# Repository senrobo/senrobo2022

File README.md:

# Sentinels Robotics

Yay we passed the 100th commit milestone
400 Commit milestone

## Checklist

### Mechanical

- Kicker Done on 20/1/2022

### Parts used

| Part Name    | Part Description                                               |
| ------------ | -------------------------------------------------------------- |
| OpenMV H7/R7 | Camera                                                         |
| MUX          | Multiplexer (https://www.ti.com/lit/ds/symlink/cd74hc4067.pdf) |

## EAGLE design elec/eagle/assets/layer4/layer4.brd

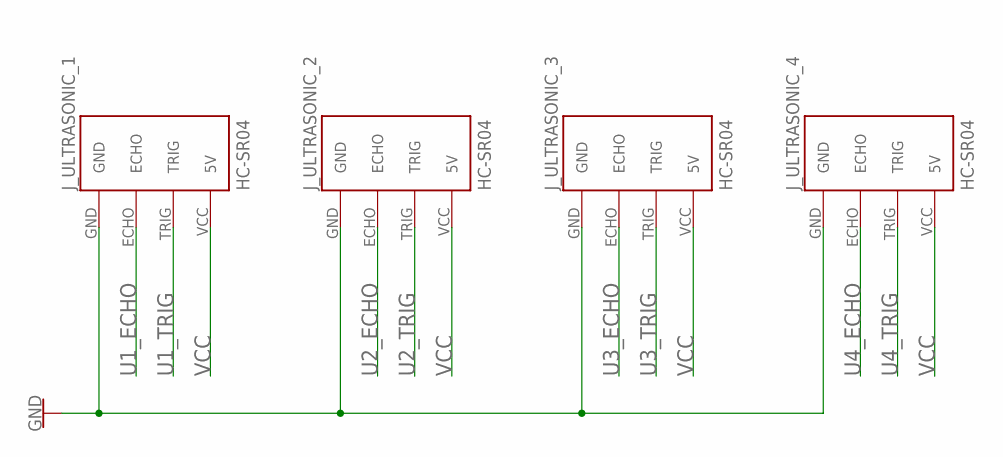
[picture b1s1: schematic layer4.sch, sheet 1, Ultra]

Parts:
J_ULTRASONIC_1, J_ULTRASONIC_2, J_ULTRASONIC_3, J_ULTRASONIC_4: HC-SR04; HC-SR04_FOOTPRINT

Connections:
GND: J_ULTRASONIC_1.GND, J_ULTRASONIC_2.GND, J_ULTRASONIC_3.GND, J_ULTRASONIC_4.GND; also elsewhere on the board
U1_ECHO: J_ULTRASONIC_1.ECHO; also elsewhere on the board
U1_TRIG: J_ULTRASONIC_1.TRIG; also elsewhere on the board
U2_ECHO: J_ULTRASONIC_2.ECHO; also elsewhere on the board
U2_TRIG: J_ULTRASONIC_2.TRIG; also elsewhere on the board
U3_ECHO: J_ULTRASONIC_3.ECHO; also elsewhere on the board
U3_TRIG: J_ULTRASONIC_3.TRIG; also elsewhere on the board
U4_ECHO: J_ULTRASONIC_4.ECHO; also elsewhere on the board
U4_TRIG: J_ULTRASONIC_4.TRIG; also elsewhere on the board
VCC: J_ULTRASONIC_1.VCC (5V), J_ULTRASONIC_2.VCC (5V), J_ULTRASONIC_3.VCC (5V), J_ULTRASONIC_4.VCC (5V); also elsewhere on the board

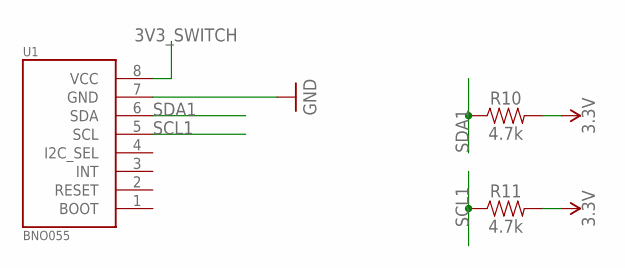
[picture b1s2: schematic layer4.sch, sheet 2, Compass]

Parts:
R10, R11: 4.7k; 0603
U1: BNO055

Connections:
3.3V: R10.2, R11.2
3V3_SWITCH: U1.8 (VCC); also elsewhere on the board
GND: U1.7 (GND); also elsewhere on the board
SCL1: R11.1, U1.5 (SCL); also elsewhere on the board
SDA1: R10.1, U1.6 (SDA); also elsewhere on the board

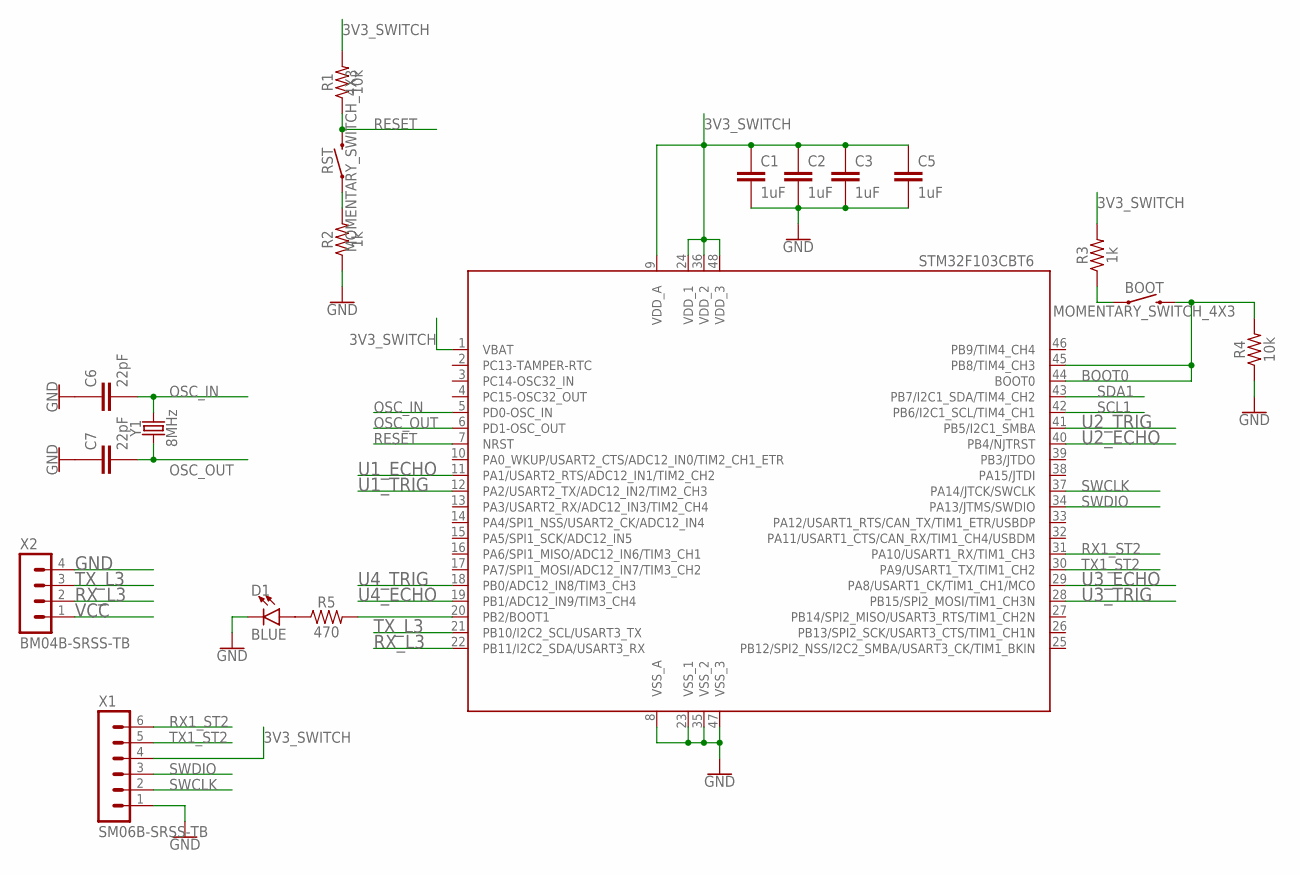
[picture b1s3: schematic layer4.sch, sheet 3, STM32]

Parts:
BOOT: MOMENTARY_SWITCH_4X3
C1, C2, C3, C5: 1uF; C0603
C6, C7: 22pF; C0603
D1: BLUE; LED-0603
R1, R4: 10k; R0603
R2, R3: 1k; R0603
R5: 470; R0603
RST: MOMENTARY_SWITCH_4X3
STM32_IR: STM32F103CBT6; LQFP48
X1: SM06B-SRSS-TB
X2: BM04B-SRSS-TB
Y1: 8MHz; CRYSTAL-SMD-5X3.2-2PAD

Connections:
3V3_SWITCH: C1.1, C2.1, C3.1, C5.2, R1.2, R3.2, STM32_IR.1 (VBAT), STM32_IR.9 (VDD_A), STM32_IR.24 (VDD_1), STM32_IR.36 (VDD_2), STM32_IR.48 (VDD_3), X1.4; also elsewhere on the board
BOOT0: BOOT.P$2 (2), R4.2, STM32_IR.44 (BOOT0), STM32_IR.45 (PB8/TIM4_CH3)
GND: C1.2, C2.2, C3.2, C5.1, C6.1, C7.1, D1.C, R2.1, R4.1, STM32_IR.8 (VSS_A), STM32_IR.23 (VSS_1), STM32_IR.35 (VSS_2), STM32_IR.47 (VSS_3), X1.1, X2.4; also elsewhere on the board
unnamed: R2.2, RST.P$1 (1)
unnamed: BOOT.P$1 (1), R3.1
unnamed: R5.2, STM32_IR.20 (PB2/BOOT1)
unnamed: D1.A, R5.1
OSC_IN: C6.2, STM32_IR.5 (PD0-OSC_IN), Y1.P$2 (2)
OSC_OUT: C7.2, STM32_IR.6 (PD1-OSC_OUT), Y1.P$1 (1)
RESET: R1.1, RST.P$2 (2), STM32_IR.7 (NRST)
RX1_ST2: STM32_IR.31 (PA10/USART1_RX/TIM1_CH3), X1.6
RX_L3: STM32_IR.22 (PB11/I2C2_SDA/USART3_RX), X2.2
SCL1: STM32_IR.42 (PB6/I2C1_SCL/TIM4_CH1); also elsewhere on the board
SDA1: STM32_IR.43 (PB7/I2C1_SDA/TIM4_CH2); also elsewhere on the board
SWCLK: STM32_IR.37 (PA14/JTCK/SWCLK), X1.2
SWDIO: STM32_IR.34 (PA13/JTMS/SWDIO), X1.3
TX1_ST2: STM32_IR.30 (PA9/USART1_TX/TIM1_CH2), X1.5
TX_L3: STM32_IR.21 (PB10/I2C2_SCL/USART3_TX), X2.3
U1_ECHO: STM32_IR.11 (PA1/USART2_RTS/ADC12_IN1/TIM2_CH2); also elsewhere on the board
U1_TRIG: STM32_IR.12 (PA2/USART2_TX/ADC12_IN2/TIM2_CH3); also elsewhere on the board
U2_ECHO: STM32_IR.40 (PB4/NJTRST); also elsewhere on the board
U2_TRIG: STM32_IR.41 (PB5/I2C1_SMBA); also elsewhere on the board
U3_ECHO: STM32_IR.29 (PA8/USART1_CK/TIM1_CH1/MCO); also elsewhere on the board
U3_TRIG: STM32_IR.28 (PB15/SPI2_MOSI/TIM1_CH3N); also elsewhere on the board
U4_ECHO: STM32_IR.19 (PB1/ADC12_IN9/TIM3_CH4); also elsewhere on the board
U4_TRIG: STM32_IR.18 (PB0/ADC12_IN8/TIM3_CH3); also elsewhere on the board
VCC: X2.1; also elsewhere on the board

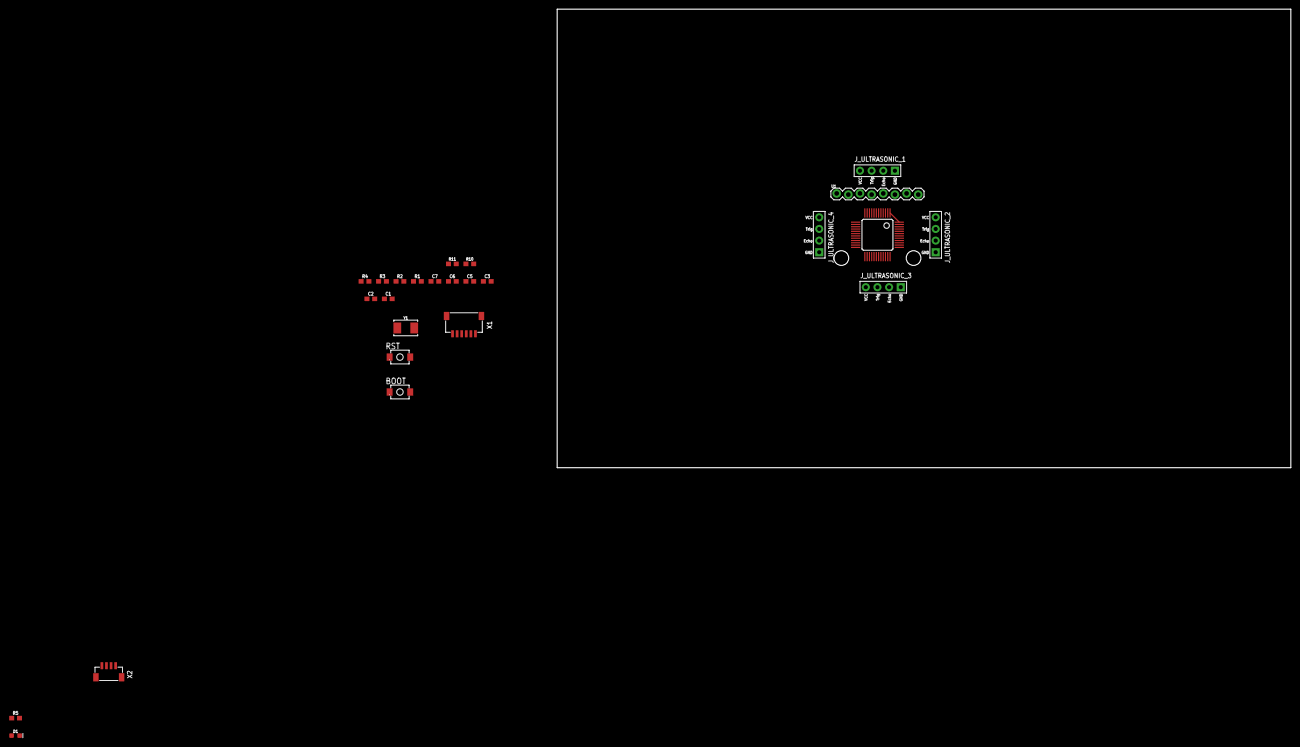
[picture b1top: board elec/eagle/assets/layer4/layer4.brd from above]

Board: 2 copper layers, 160.0 x 100.0 mm, 25 parts (0 on the bottom side), 28 nets.

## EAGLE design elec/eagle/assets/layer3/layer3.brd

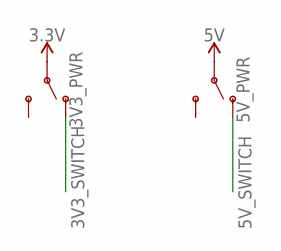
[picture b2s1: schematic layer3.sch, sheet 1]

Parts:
3V3_PWR, 5V_PWR: SWITCH-SPDT-PTH-11.6X4.0MM-LOCK; SWITCH_SPDT_PTH_11.6X4.0MM_LOCK

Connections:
3.3V: 3V3_PWR.2; also elsewhere on the board
3V3_SWITCH: 3V3_PWR.1 (O); also elsewhere on the board
5V: 5V_PWR.2; also elsewhere on the board
5V_SWITCH: 5V_PWR.1 (O); also elsewhere on the board

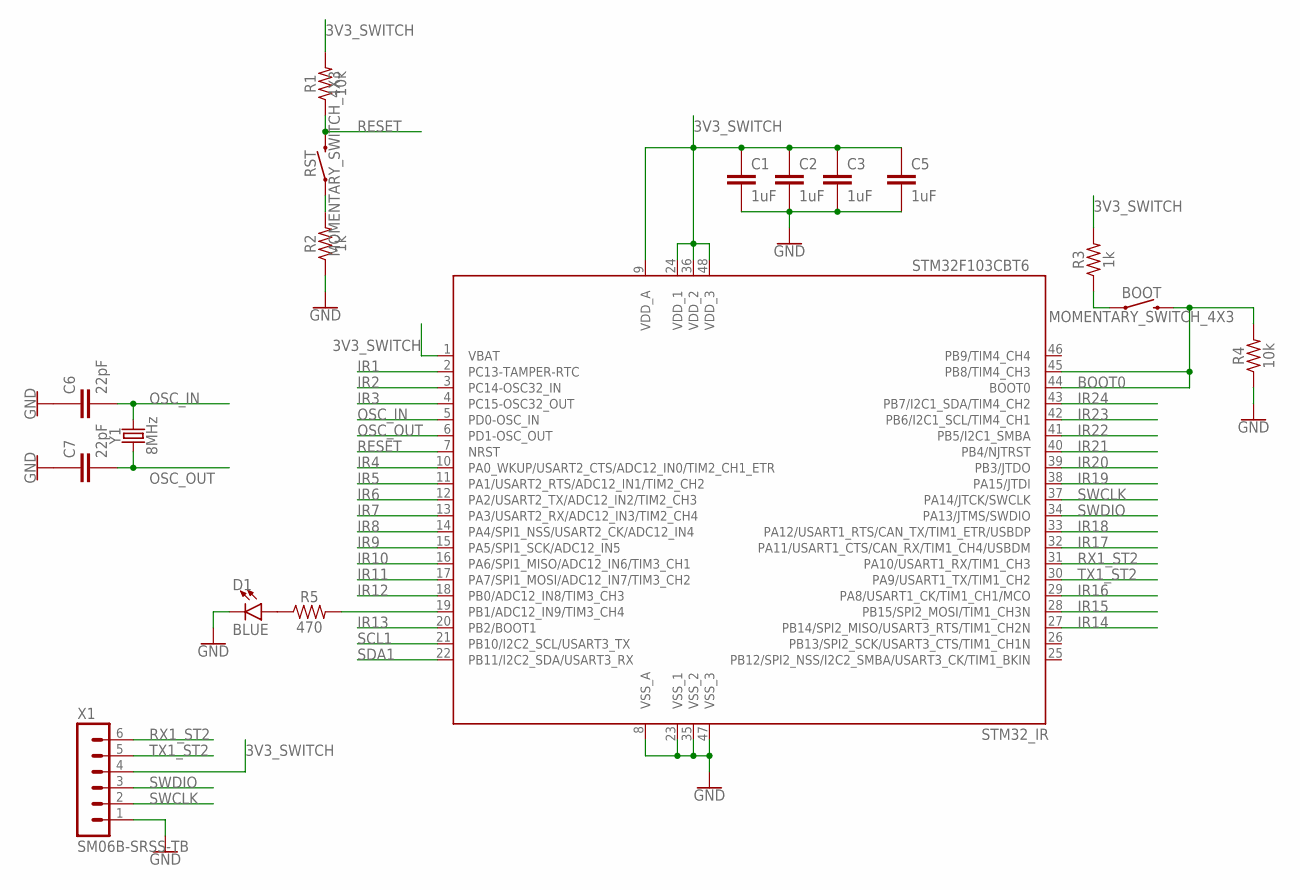
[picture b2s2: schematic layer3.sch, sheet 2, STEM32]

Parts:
BOOT: MOMENTARY_SWITCH_4X3
C1, C2, C3, C5: 1uF; C0603
C6, C7: 22pF; C0603
D1: BLUE; LED-0603
R1, R4: 10k; R0603
R2, R3: 1k; R0603
R5: 470; R0603
RST: MOMENTARY_SWITCH_4X3
STM32_IR: STM32F103CBT6; LQFP48
X1: SM06B-SRSS-TB
Y1: 8MHz; CRYSTAL-SMD-5X3.2-2PAD

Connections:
3V3_SWITCH: C1.1, C2.1, C3.1, C5.2, R1.2, R3.2, STM32_IR.1 (VBAT), STM32_IR.9 (VDD_A), STM32_IR.24 (VDD_1), STM32_IR.36 (VDD_2), STM32_IR.48 (VDD_3), X1.4; also elsewhere on the board
BOOT0: BOOT.P$2 (2), R4.2, STM32_IR.44 (BOOT0), STM32_IR.45 (PB8/TIM4_CH3)
GND: C1.2, C2.2, C3.2, C5.1, C6.1, C7.1, D1.C, R2.1, R4.1, STM32_IR.8 (VSS_A), STM32_IR.23 (VSS_1), STM32_IR.35 (VSS_2), STM32_IR.47 (VSS_3), X1.1; also elsewhere on the board
IR1: STM32_IR.2 (PC13-TAMPER-RTC); also elsewhere on the board
IR2: STM32_IR.3 (PC14-OSC32_IN); also elsewhere on the board
IR3: STM32_IR.4 (PC15-OSC32_OUT); also elsewhere on the board
IR4: STM32_IR.10 (PA0_WKUP/USART2_CTS/ADC12_IN0/TIM2_CH1_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); also elsewhere on the board
IR5: STM32_IR.11 (PA1/USART2_RTS/ADC12_IN1/TIM2_CH2); also elsewhere on the board
IR6: STM32_IR.12 (PA2/USART2_TX/ADC12_IN2/TIM2_CH3); also elsewhere on the board
IR7: STM32_IR.13 (PA3/USART2_RX/ADC12_IN3/TIM2_CH4); also elsewhere on the board
IR8: STM32_IR.14 (PA4/SPI1_NSS/USART2_CK/ADC12_IN4); also elsewhere on the board
IR9: STM32_IR.15 (PA5/SPI1_SCK/ADC12_IN5); also elsewhere on the board
IR10: STM32_IR.16 (PA6/SPI1_MISO/ADC12_IN6/TIM3_CH1); also elsewhere on the board
IR11: STM32_IR.17 (PA7/SPI1_MOSI/ADC12_IN7/TIM3_CH2); also elsewhere on the board
IR12: STM32_IR.18 (PB0/ADC12_IN8/TIM3_CH3); also elsewhere on the board
IR13: STM32_IR.20 (PB2/BOOT1); also elsewhere on the board
IR14: STM32_IR.27 (PB14/SPI2_MISO/USART3_RTS/TIM1_CH2N); also elsewhere on the board
IR15: STM32_IR.28 (PB15/SPI2_MOSI/TIM1_CH3N); also elsewhere on the board
IR16: STM32_IR.29 (PA8/USART1_CK/TIM1_CH1/MCO); also elsewhere on the board
IR17: STM32_IR.32 (PA11/USART1_CTS/CAN_RX/TIM1_CH4/USBDM); also elsewhere on the board
IR18: STM32_IR.33 (PA12/USART1_RTS/CAN_TX/TIM1_ETR/USBDP); also elsewhere on the board
IR19: STM32_IR.38 (PA15/JTDI); also elsewhere on the board
IR20: STM32_IR.39 (PB3/JTDO); also elsewhere on the board
IR21: STM32_IR.40 (PB4/NJTRST); also elsewhere on the board
IR22: STM32_IR.41 (PB5/I2C1_SMBA); also elsewhere on the board
IR23: STM32_IR.42 (PB6/I2C1_SCL/TIM4_CH1); also elsewhere on the board
IR24: STM32_IR.43 (PB7/I2C1_SDA/TIM4_CH2); also elsewhere on the board
unnamed: R2.2, RST.P$1 (1)
unnamed: BOOT.P$1 (1), R3.1
unnamed: R5.2, STM32_IR.19 (PB1/ADC12_IN9/TIM3_CH4)
unnamed: D1.A, R5.1
OSC_IN: C6.2, STM32_IR.5 (PD0-OSC_IN), Y1.P$2 (2)
OSC_OUT: C7.2, STM32_IR.6 (PD1-OSC_OUT), Y1.P$1 (1)
RESET: R1.1, RST.P$2 (2), STM32_IR.7 (NRST)
RX1_ST2: STM32_IR.31 (PA10/USART1_RX/TIM1_CH3), X1.6; also elsewhere on the board
SCL1: STM32_IR.21 (PB10/I2C2_SCL/USART3_TX)
SDA1: STM32_IR.22 (PB11/I2C2_SDA/USART3_RX)
SWCLK: STM32_IR.37 (PA14/JTCK/SWCLK), X1.2
SWDIO: STM32_IR.34 (PA13/JTMS/SWDIO), X1.3
TX1_ST2: STM32_IR.30 (PA9/USART1_TX/TIM1_CH2), X1.5; also elsewhere on the board

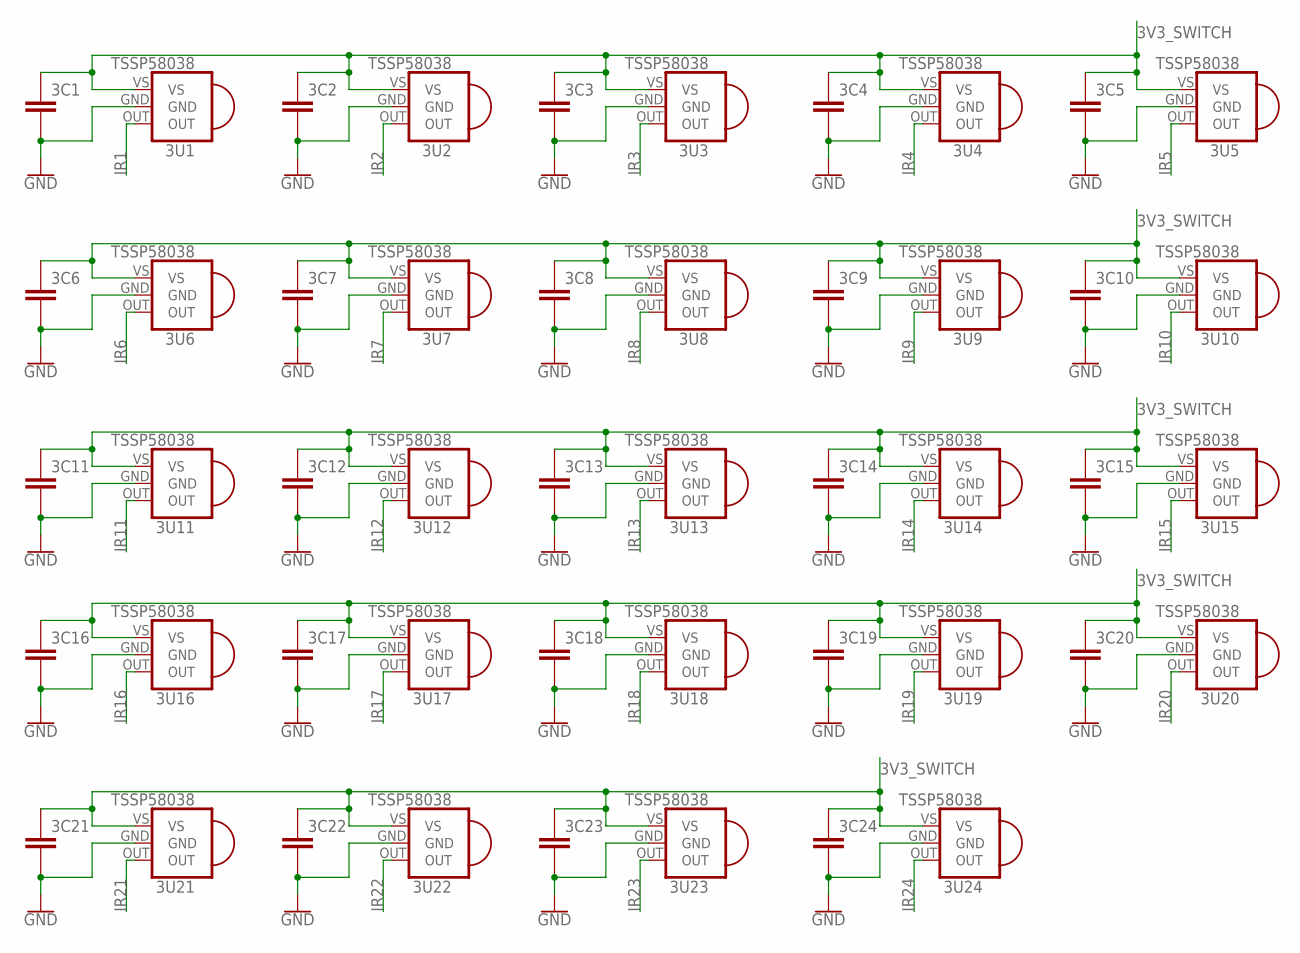
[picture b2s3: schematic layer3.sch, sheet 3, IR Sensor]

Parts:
3C1, 3C2, 3C3, 3C4, 3C5, 3C6, 3C7, 3C8, 3C9, 3C10, 3C11, 3C12, 3C13, 3C14, 3C15, 3C16, 3C17, 3C18, 3C19, 3C20, 3C21, 3C22, 3C23, 3C24: CAPACITOR0603; C0603
3U1, 3U2, 3U3, 3U4, 3U5, 3U6, 3U7, 3U8, 3U9, 3U10, 3U11, 3U12, 3U13, 3U14, 3U15, 3U16, 3U17, 3U18, 3U19, 3U20, 3U21, 3U22, 3U23, 3U24: TSSP58038

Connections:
3V3_SWITCH: 3C1.1, 3C2.1, 3C3.1, 3C4.1, 3C5.1, 3C6.1, 3C7.1, 3C8.1, 3C9.1, 3C10.1, 3C11.1, 3C12.1, 3C13.1, 3C14.1, 3C15.1, 3C16.1, 3C17.1, 3C18.1, 3C19.1, 3C20.1, 3C21.1, 3C22.1, 3C23.1, 3C24.1, 3U1.VS, 3U2.VS, 3U3.VS, 3U4.VS, 3U5.VS, 3U6.VS, 3U7.VS, 3U8.VS, 3U9.VS, 3U10.VS, 3U11.VS, 3U12.VS, 3U13.VS, 3U14.VS, 3U15.VS, 3U16.VS, 3U17.VS, 3U18.VS, 3U19.VS, 3U20.VS, 3U21.VS, 3U22.VS, 3U23.VS, 3U24.VS; also elsewhere on the board
GND: 3C1.2, 3C2.2, 3C3.2, 3C4.2, 3C5.2, 3C6.2, 3C7.2, 3C8.2, 3C9.2, 3C10.2, 3C11.2, 3C12.2, 3C13.2, 3C14.2, 3C15.2, 3C16.2, 3C17.2, 3C18.2, 3C19.2, 3C20.2, 3C21.2, 3C22.2, 3C23.2, 3C24.2, 3U1.GND, 3U2.GND, 3U3.GND, 3U4.GND, 3U5.GND, 3U6.GND, 3U7.GND, 3U8.GND, 3U9.GND, 3U10.GND, 3U11.GND, 3U12.GND, 3U13.GND, 3U14.GND, 3U15.GND, 3U16.GND, 3U17.GND, 3U18.GND, 3U19.GND, 3U20.GND, 3U21.GND, 3U22.GND, 3U23.GND, 3U24.GND; also elsewhere on the board
IR1: 3U1.OUT; also elsewhere on the board
IR2: 3U2.OUT; also elsewhere on the board
IR3: 3U3.OUT; also elsewhere on the board
IR4: 3U4.OUT; also elsewhere on the board
IR5: 3U5.OUT; also elsewhere on the board
IR6: 3U6.OUT; also elsewhere on the board
IR7: 3U7.OUT; also elsewhere on the board
IR8: 3U8.OUT; also elsewhere on the board
IR9: 3U9.OUT; also elsewhere on the board
IR10: 3U10.OUT; also elsewhere on the board
IR11: 3U11.OUT; also elsewhere on the board
IR12: 3U12.OUT; also elsewhere on the board
IR13: 3U13.OUT; also elsewhere on the board
IR14: 3U14.OUT; also elsewhere on the board
IR15: 3U15.OUT; also elsewhere on the board
IR16: 3U16.OUT; also elsewhere on the board
IR17: 3U17.OUT; also elsewhere on the board
IR18: 3U18.OUT; also elsewhere on the board
IR19: 3U19.OUT; also elsewhere on the board
IR20: 3U20.OUT; also elsewhere on the board
IR21: 3U21.OUT; also elsewhere on the board
IR22: 3U22.OUT; also elsewhere on the board
IR23: 3U23.OUT; also elsewhere on the board
IR24: 3U24.OUT; also elsewhere on the board

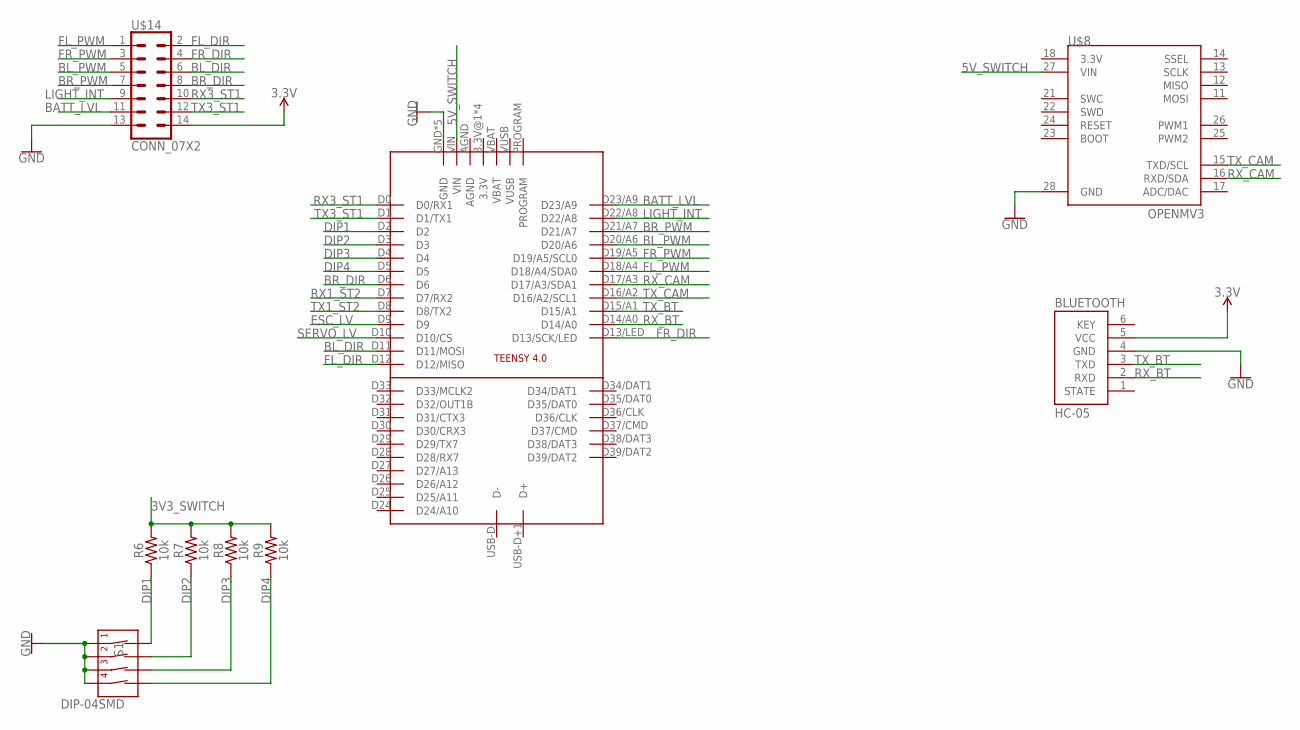
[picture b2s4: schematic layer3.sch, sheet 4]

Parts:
BLUETOOTH: HC-05
R6, R7, R8, R9: 10k; R0603
S1: DIP-04SMD; DIPSWITCH-04-SMD
TEENSY4: TEENSY-4.0-FULL-BREAKOUT-PINS
U$8: OPENMV3
U$14: CONN_07X2; 2X7

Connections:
3.3V: BLUETOOTH.5 (VCC), U$14.14; also elsewhere on the board
3V3_SWITCH: R6.2, R7.2, R8.2, R9.2; also elsewhere on the board
5V_SWITCH: TEENSY4.VIN, U$8.27 (VIN); also elsewhere on the board
BATT_LVL: TEENSY4.D23/A9, U$14.11
BL_DIR: TEENSY4.D11 (D11/MOSI), U$14.6
BL_PWM: TEENSY4.D20/A6, U$14.5
BR_DIR: TEENSY4.D6, U$14.8
BR_PWM: TEENSY4.D21/A7, U$14.7
DIP1: R6.1, S1.1 (1A), TEENSY4.D2
DIP2: R7.1, S1.2 (2A), TEENSY4.D3
DIP3: R8.1, S1.3 (3A), TEENSY4.D4
DIP4: R9.1, S1.4 (4A), TEENSY4.D5
ESC_LV: TEENSY4.D9; also elsewhere on the board
FL_DIR: TEENSY4.D12 (D12/MISO), U$14.2
FL_PWM: TEENSY4.D18/A4 (D18/A4/SDA0), U$14.1
FR_DIR: TEENSY4.D13/LED (D13/SCK/LED), U$14.4
FR_PWM: TEENSY4.D19/A5 (D19/A5/SCL0), U$14.3
GND: BLUETOOTH.4 (GND), S1.5 (4B), S1.6 (3B), S1.7 (2B), S1.8 (1B), TEENSY4.GND, TEENSY4.GND@1 (GND), TEENSY4.GND@2 (GND), TEENSY4.P$11 (GND), TEENSY4.P$12 (GND), U$8.28 (GND), U$14.13; also elsewhere on the board
LIGHT_INT: TEENSY4.D22/A8, U$14.9
RX1_ST2: TEENSY4.D7 (D7/RX2); also elsewhere on the board
RX3_ST1: TEENSY4.D0 (D0/RX1), U$14.10
RX_BT: BLUETOOTH.2 (RXD), TEENSY4.D14/A0
RX_CAM: TEENSY4.D17/A3 (D17/A3/SDA1), U$8.16 (RXD/SDA)
SERVO_LV: TEENSY4.D10 (D10/CS); also elsewhere on the board
TX1_ST2: TEENSY4.D8 (D8/TX2); also elsewhere on the board
TX3_ST1: TEENSY4.D1 (D1/TX1), U$14.12
TX_BT: BLUETOOTH.3 (TXD), TEENSY4.D15/A1
TX_CAM: TEENSY4.D16/A2 (D16/A2/SCL1), U$8.15 (TXD/SCL)

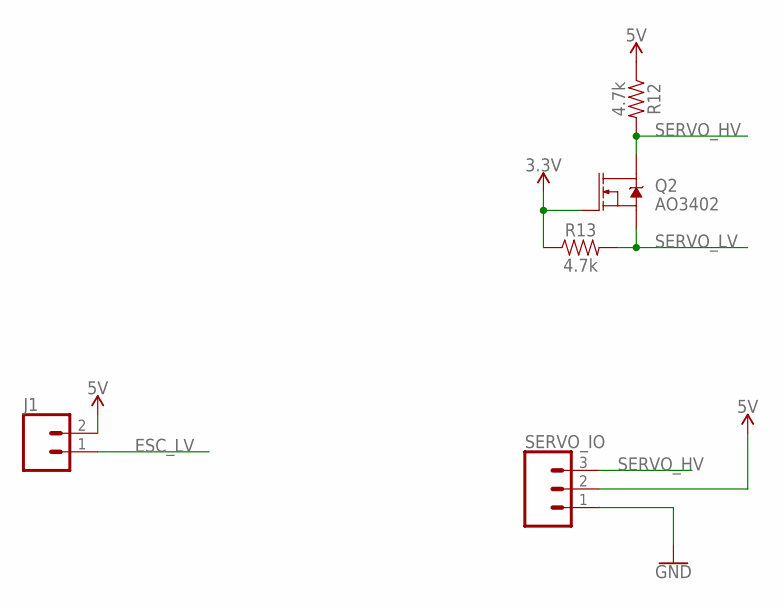
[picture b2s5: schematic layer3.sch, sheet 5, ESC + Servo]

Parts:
J1: CONN_02LOCK; 1X02_LOCK
Q2: AO3402; SOT23-3
R12, R13: 4.7k; R0603
SERVO_IO: CONN_03LOCK; 1X03_LOCK

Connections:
3.3V: Q2.1 (G), R13.1; also elsewhere on the board
5V: J1.2, R12.1, SERVO_IO.2; also elsewhere on the board
ESC_LV: J1.1; also elsewhere on the board
GND: SERVO_IO.1; also elsewhere on the board
SERVO_HV: Q2.3 (D), R12.2, SERVO_IO.3
SERVO_LV: Q2.2 (S), R13.2; also elsewhere on the board

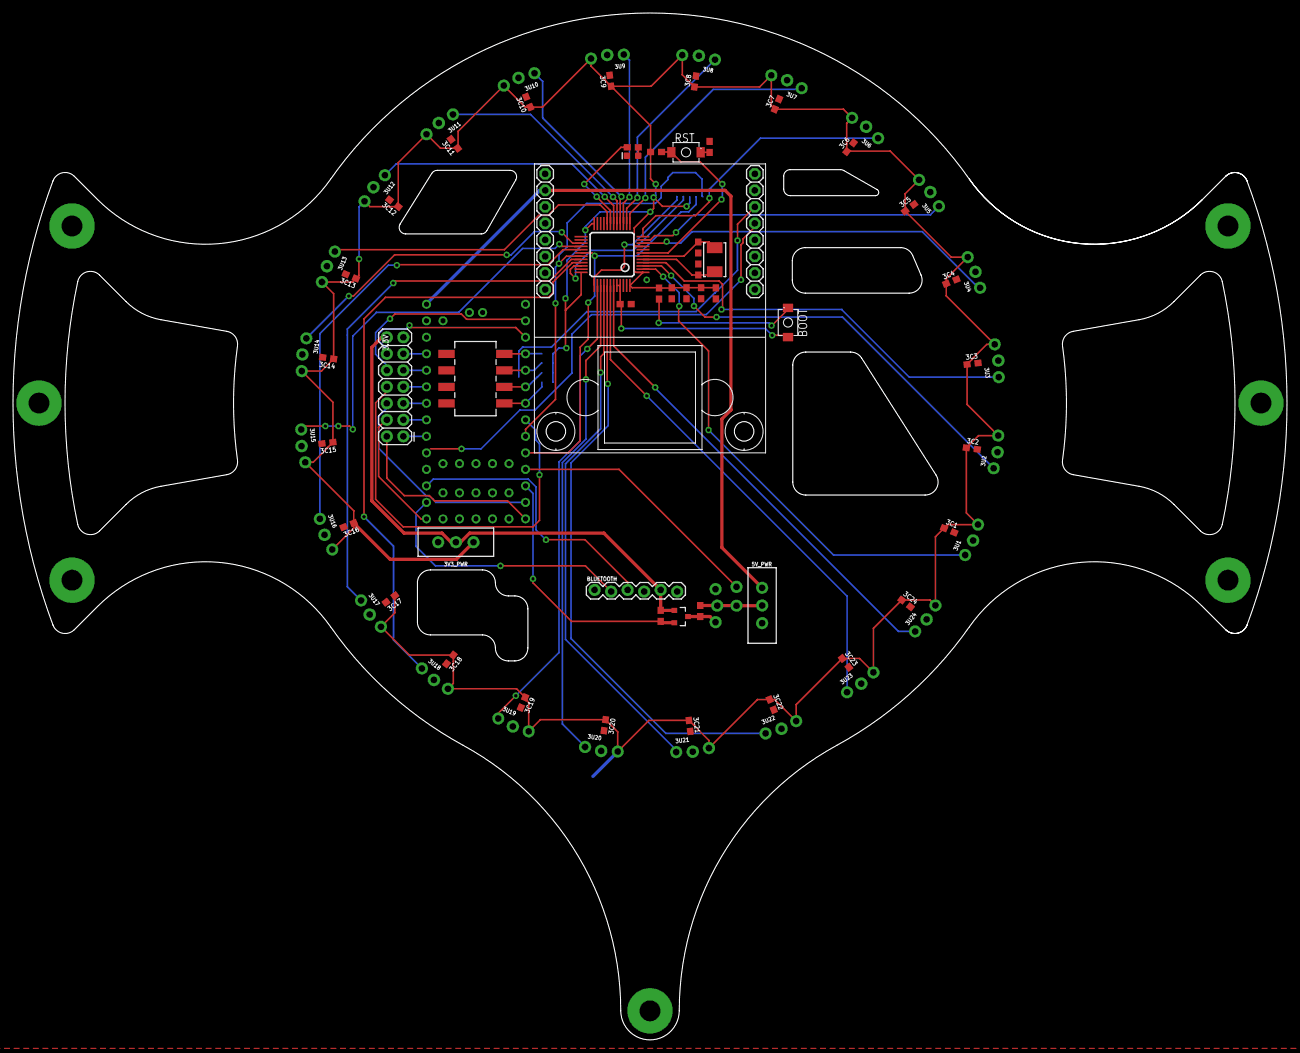
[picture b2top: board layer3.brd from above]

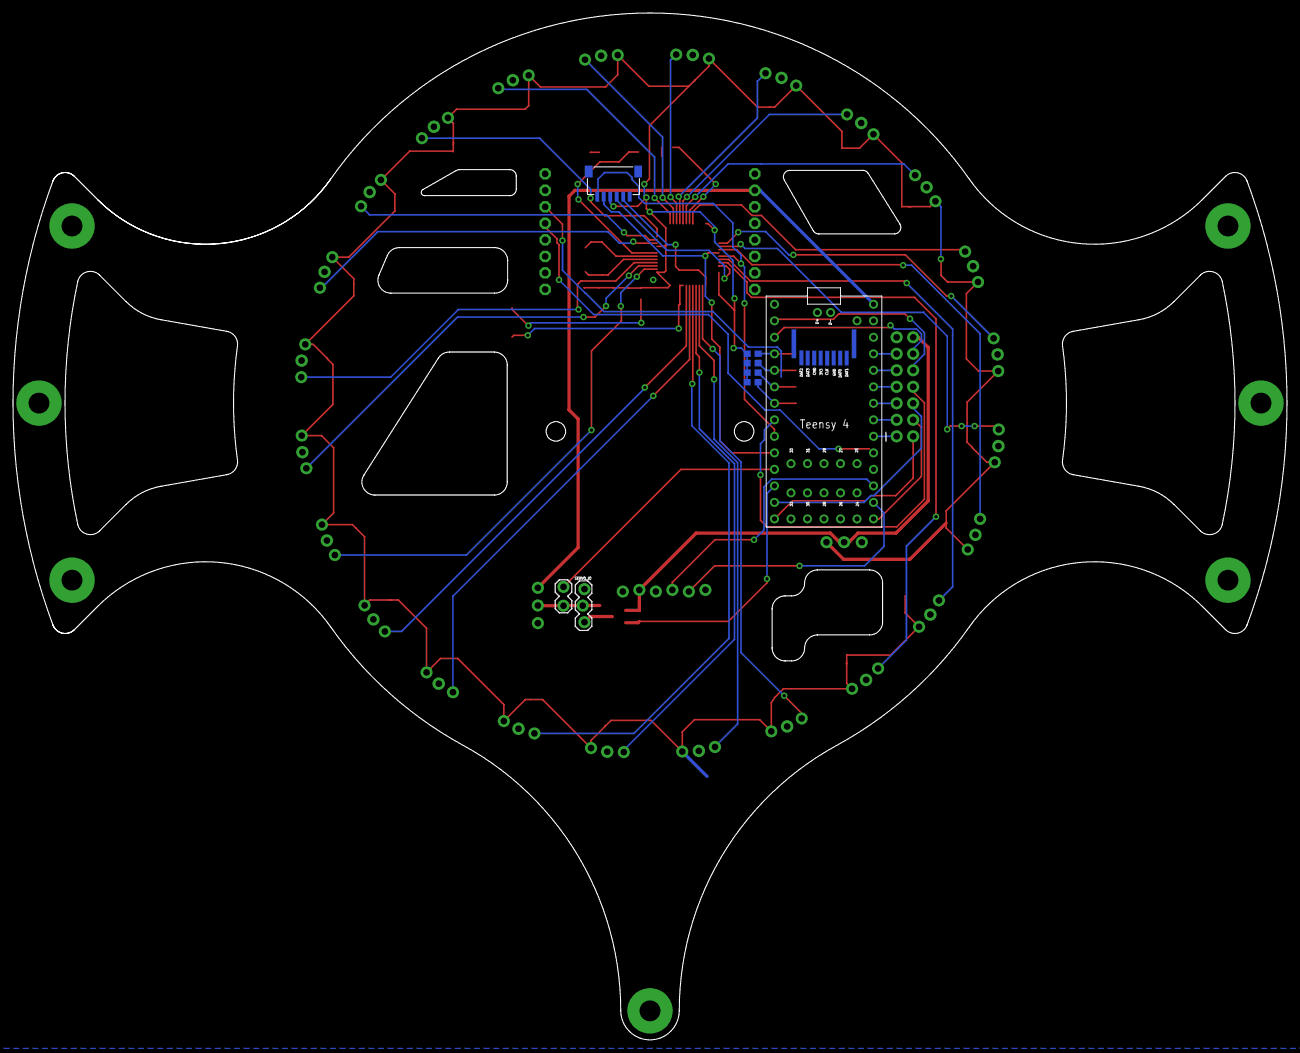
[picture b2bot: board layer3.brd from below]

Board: 2 copper layers, 196.0 x 158.0 mm, 81 parts (8 on the bottom side), 64 nets.

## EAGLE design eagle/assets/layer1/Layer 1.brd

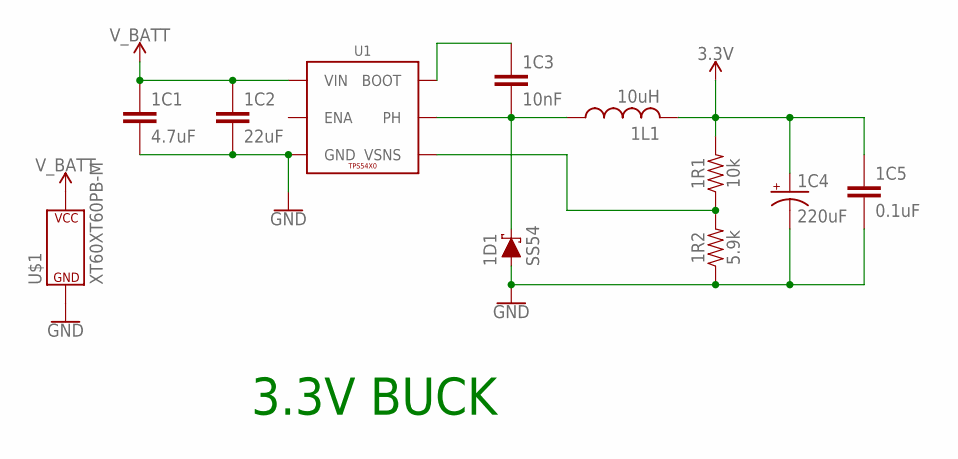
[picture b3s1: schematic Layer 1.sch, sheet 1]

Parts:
1C1: 4.7uF; C0603
1C2: 22uF; C1210
1C3: 10nF; C0603
1C4: 220uF; EIA7343
1C5: 0.1uF; C0603
1D1: SS54; SMA-DIODE
1L1: 10uH; SWPA8040
1R1: 10k; R0603
1R2: 5.9k; R0603
U1: TPS54X0; POWERPAD-SOIC-8
U$1: XT60XT60PB-M; XT60PB-M

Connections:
3.3V: 1C4.A (+), 1C5.1, 1L1.P2 (2), 1R1.2; also elsewhere on the board
GND: 1C1.2, 1C2.2, 1C4.C (-), 1C5.2, 1D1.A, 1R2.1, U1.6 (GND), U1.9 (GND), U1.P$1 (GND), U1.P$2 (GND), U1.P$3 (GND), U1.P$4 (GND), U1.P$5 (GND), U1.P$6 (GND), U$1.- (V-); also elsewhere on the board
unnamed: 1C3.1, U1.1 (BOOT)
unnamed: 1C3.2, 1D1.C, 1L1.P1 (1), U1.8 (PH)
unnamed: 1R1.1, 1R2.2, U1.4 (VSNS)
V_BATT: 1C1.1, 1C2.1, U1.7 (VIN), U$1.+ (V+); also elsewhere on the board

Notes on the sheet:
3.3V BUCK

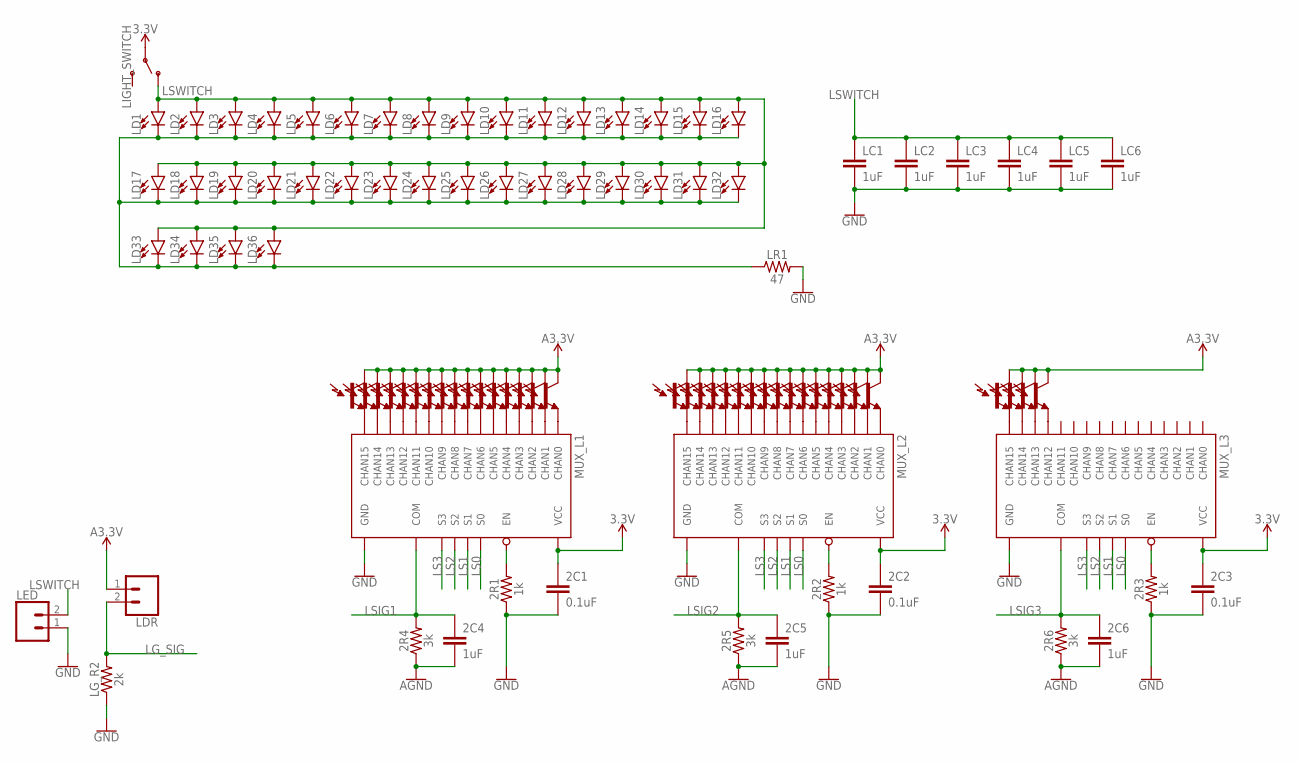
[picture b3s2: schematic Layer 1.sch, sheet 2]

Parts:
2C1, 2C2, 2C3: 0.1uF; C0603
2C4, 2C5, 2C6: 1uF; C0603
2R1, 2R2, 2R3: 1k; R0603
2R4, 2R5, 2R6: 3k; R0603
LC1, LC2, LC3, LC4, LC5, LC6: 1uF; C0603
LD1, LD2, LD3, LD4, LD5, LD6, LD7, LD8, LD9, LD10, LD11, LD12, LD13, LD14, LD15, LD16, LD17, LD18, LD19, LD20, LD21, LD22, LD23, LD24, LD25, LD26, LD27, LD28, LD29, LD30, LD31, LD32, LD33, LD34, LD35, LD36: 3528LED; 3528
LDR: CONN_021X02_NO_SILK; 1X02_NO_SILK
LED: CONN_02POLAR; MOLEX-1X2
LG_R2: 2k; R0603
LIGHT_SWITCH: SWITCH-SPDT-PTH-11.6X4.0MM-LOCK; SWITCH_SPDT_PTH_11.6X4.0MM_LOCK
LR1: 47; R0603
MUX_L1, MUX_L2, MUX_L3: 74HC4067SSOP-24; SSOP24
Q1, Q2, Q3, Q4, Q5, Q6, Q7, Q8, Q9, Q10, Q11, Q12, Q13, Q14, Q15, Q16, Q17, Q18, Q19, Q20, Q21, Q22, Q23, Q24, Q25, Q26, Q27, Q28, Q29, Q30, Q31, Q32, Q33, Q34, Q35, Q36: LIGHT_SENSORALS; ALS-PT19

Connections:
3.3V: 2C1.1, 2C2.1, 2C3.1, LIGHT_SWITCH.2, MUX_L1.24 (VCC), MUX_L2.24 (VCC), MUX_L3.24 (VCC); also elsewhere on the board
AGND: 2C4.2, 2C5.2, 2C6.2, 2R4.1, 2R5.1, 2R6.1; also elsewhere on the board
GND: 2C1.2, 2C2.2, 2C3.2, 2R1.1, 2R2.1, 2R3.1, LC1.2, LC2.2, LC3.2, LC4.2, LC5.2, LC6.2, LED.1, LG_R2.1, LR1.2, MUX_L1.12 (GND), MUX_L2.12 (GND), MUX_L3.12 (GND); also elsewhere on the board
LG_SIG: LDR.2, LG_R2.2; also elsewhere on the board
LS0: MUX_L1.10 (S0), MUX_L2.10 (S0), MUX_L3.10 (S0); also elsewhere on the board
LS1: MUX_L1.11 (S1), MUX_L2.11 (S1), MUX_L3.11 (S1); also elsewhere on the board
LS2: MUX_L1.14 (S2), MUX_L2.14 (S2), MUX_L3.14 (S2); also elsewhere on the board
LS3: MUX_L1.13 (S3), MUX_L2.13 (S3), MUX_L3.13 (S3); also elsewhere on the board
LSIG1: 2C4.1, 2R4.2, MUX_L1.1 (COM); also elsewhere on the board
LSIG2: 2C5.1, 2R5.2, MUX_L2.1 (COM); also elsewhere on the board
LSIG3: 2C6.1, 2R6.2, MUX_L3.1 (COM); also elsewhere on the board
LSWITCH: LC1.1, LC2.1, LC3.1, LC4.1, LC5.1, LC6.1, LD1.A, LD2.A, LD3.A, LD4.A, LD5.A, LD6.A, LD7.A, LD8.A, LD9.A, LD10.A, LD11.A, LD12.A, LD13.A, LD14.A, LD15.A, LD16.A, LD17.A, LD18.A, LD19.A, LD20.A, LD21.A, LD22.A, LD23.A, LD24.A, LD25.A, LD26.A, LD27.A, LD28.A, LD29.A, LD30.A, LD31.A, LD32.A, LD33.A, LD34.A, LD35.A, LD36.A, LED.2, LIGHT_SWITCH.1 (O)
unnamed: 2R1.2, MUX_L1.15 (EN)
unnamed: MUX_L1.16 (CHAN15), Q1.E (E1)
unnamed: MUX_L1.17 (CHAN14), Q2.E (E1)
unnamed: MUX_L1.18 (CHAN13), Q3.E (E1)
unnamed: MUX_L1.19 (CHAN12), Q4.E (E1)
unnamed: MUX_L1.20 (CHAN11), Q5.E (E1)
unnamed: MUX_L1.21 (CHAN10), Q6.E (E1)
unnamed: MUX_L1.22 (CHAN9), Q7.E (E1)
unnamed: MUX_L1.23 (CHAN8), Q8.E (E1)
unnamed: MUX_L1.2 (CHAN7), Q9.E (E1)
unnamed: MUX_L1.3 (CHAN6), Q10.E (E1)
unnamed: MUX_L1.4 (CHAN5), Q11.E (E1)
unnamed: MUX_L1.5 (CHAN4), Q12.E (E1)
unnamed: MUX_L1.6 (CHAN3), Q13.E (E1)
unnamed: MUX_L1.7 (CHAN2), Q14.E (E1)
unnamed: MUX_L1.8 (CHAN1), Q15.E (E1)
unnamed: MUX_L1.9 (CHAN0), Q16.E (E1)
unnamed: LD1.C, LD2.C, LD3.C, LD4.C, LD5.C, LD6.C, LD7.C, LD8.C, LD9.C, LD10.C, LD11.C, LD12.C, LD13.C, LD14.C, LD15.C, LD16.C, LD17.C, LD18.C, LD19.C, LD20.C, LD21.C, LD22.C, LD23.C, LD24.C, LD25.C, LD26.C, LD27.C, LD28.C, LD29.C, LD30.C, LD31.C, LD32.C, LD33.C, LD34.C, LD35.C, LD36.C, LR1.1
unnamed: 2R2.2, MUX_L2.15 (EN)
unnamed: MUX_L2.16 (CHAN15), Q17.E (E1)
unnamed: MUX_L2.17 (CHAN14), Q18.E (E1)
unnamed: MUX_L2.18 (CHAN13), Q19.E (E1)
unnamed: MUX_L2.19 (CHAN12), Q20.E (E1)
unnamed: MUX_L2.20 (CHAN11), Q21.E (E1)
unnamed: MUX_L2.21 (CHAN10), Q22.E (E1)
unnamed: MUX_L2.22 (CHAN9), Q23.E (E1)
unnamed: MUX_L2.23 (CHAN8), Q24.E (E1)
unnamed: MUX_L2.2 (CHAN7), Q25.E (E1)
unnamed: MUX_L2.3 (CHAN6), Q26.E (E1)
unnamed: MUX_L2.4 (CHAN5), Q27.E (E1)
unnamed: MUX_L2.5 (CHAN4), Q28.E (E1)
unnamed: MUX_L2.6 (CHAN3), Q29.E (E1)
unnamed: MUX_L2.7 (CHAN2), Q30.E (E1)
unnamed: MUX_L2.8 (CHAN1), Q31.E (E1)
unnamed: MUX_L2.9 (CHAN0), Q32.E (E1)
unnamed: 2R3.2, MUX_L3.15 (EN)
unnamed: MUX_L3.16 (CHAN15), Q33.E (E1)
unnamed: MUX_L3.17 (CHAN14), Q34.E (E1)
unnamed: MUX_L3.18 (CHAN13), Q35.E (E1)
unnamed: MUX_L3.19 (CHAN12), Q36.E (E1)
VCCA: LDR.1, Q1.C (C1), Q2.C (C1), Q3.C (C1), Q4.C (C1), Q5.C (C1), Q6.C (C1), Q7.C (C1), Q8.C (C1), Q9.C (C1), Q10.C (C1), Q11.C (C1), Q12.C (C1), Q13.C (C1), Q14.C (C1), Q15.C (C1), Q16.C (C1), Q17.C (C1), Q18.C (C1), Q19.C (C1), Q20.C (C1), Q21.C (C1), Q22.C (C1), Q23.C (C1), Q24.C (C1), Q25.C (C1), Q26.C (C1), Q27.C (C1), Q28.C (C1), Q29.C (C1), Q30.C (C1), Q31.C (C1), Q32.C (C1), Q33.C (C1), Q34.C (C1), Q35.C (C1), Q36.C (C1); also elsewhere on the board

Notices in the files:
parts and their libraries:
SparkFun-Capacitors: Licensing: Creative Commons ShareAlike 4.0 International - https://creativecommons.org/licenses/by-sa/4.0
